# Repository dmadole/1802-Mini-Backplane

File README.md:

# 1802-Mini-Backplane

This is a backplane for the [1802/Mini](https://github.com/dmadole/1802-Mini) system. It supports the following features:

* Seven slots using 1x39 single-row header sockets
* Power, reset, and, and input pushbuttons
* Power input via mini-USB or 2.1mm barrel jack
* USB pass-through header, can also be used for power
* Boards can be coupled end-to-end to make larger backplanes
* PCB can also be assembled as a slot extender card
* Optional pull-up resistors for TPA, TPB, and CLOCK

Gerber files for the PCBs and PDF schematics can be found in [Releases](https://github.com/dmadole/1802-Mini-Backplane/releases).

BOMS and any applicable errata or other notes can be found in [notes](https://github.com/dmadole/1802-Mini-Backplane/tree/main/notes).

For availability of kits and bare PCBs please see http://madole.net/1802/mini/kits

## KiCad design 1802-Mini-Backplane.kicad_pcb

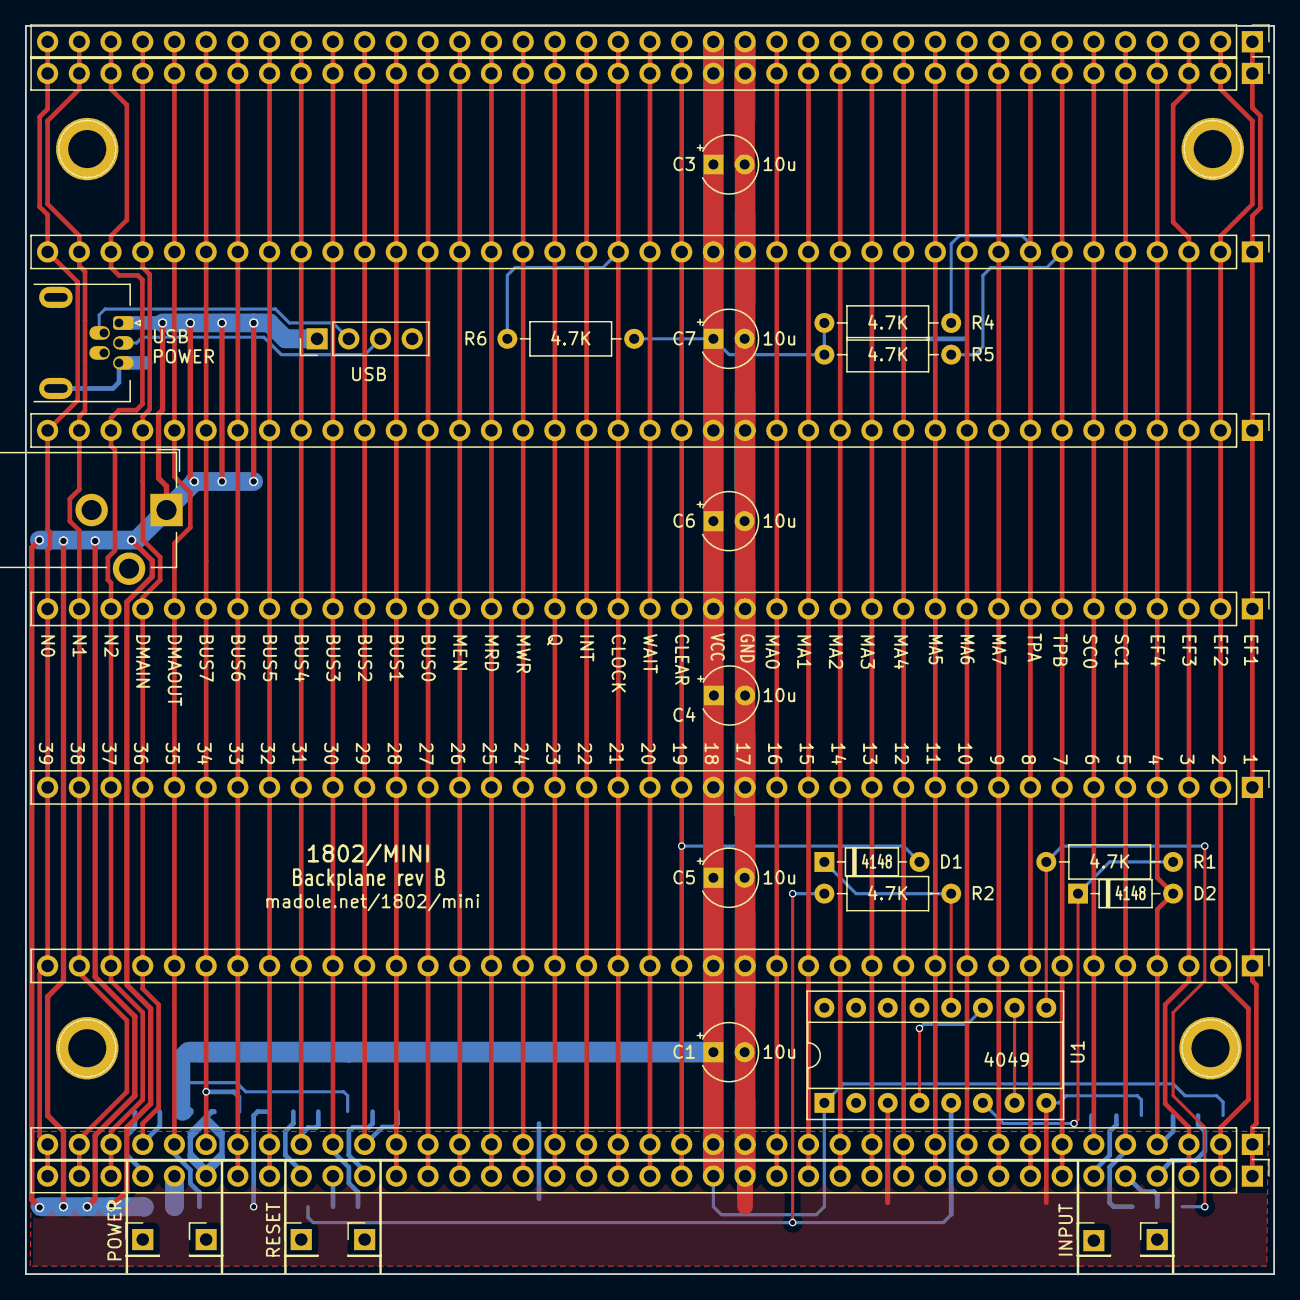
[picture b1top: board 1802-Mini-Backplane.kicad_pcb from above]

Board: 2 copper layers, 100.0 x 100.0 mm, 45 parts (0 on the bottom side), 57 nets.

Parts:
C1, C3, C4, C5, C6, C7: 10uF; CP_Radial_Tantal_D4.5mm_P2.50mm
D1, D2: 1N4148; D_DO-35_SOD27_P7.62mm_Horizontal
J1: Barrel_Jack_Switch; BarrelJack_CUI_PJ-102AH_Horizontal
J2, J3, J4, J5, J6, J7, J8, J14, J15: Expansion; PinHeader_1x39_P2.54mm_Vertical
J9, J10, J11, J12: Mount; 1pin
J13: 56579-0519; USB_Mini-AB_Molex_56579_0519
J16, J17, J18, J19, J20, J21: Mount; PinHeader_1x01_P2.54mm_Vertical
J22: Conn_01x04; PinHeader_1x04_P2.54mm_Vertical
JP1, JP2, JP3, JP4, JP5, JP6, JP7, JP8, JP9: Jumper_3_Open; SolderJumper-3_P2.0mm_Open_TrianglePad1.0x1.5mm_NumberLabels
R1, R2, R4, R5, R6: 4.7K; R_Axial_DIN0207_L6.3mm_D2.5mm_P10.16mm_Horizontal
U1: 4049; DIP-16_W7.62mm_Socket

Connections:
/BUS0: J2.27, J3.27, J4.27, J5.27, J6.27, J7.27, J8.27, J14.27, J15.27
/BUS1: J2.28, J3.28, J4.28, J5.28, J6.28, J7.28, J8.28, J14.28, J15.28
/BUS2: J2.29, J3.29, J4.29, J5.29, J6.29, J7.29, J8.29, J14.29, JP4.3
/BUS3: J2.30, J3.30, J4.30, J5.30, J6.30, J7.30, J8.30, J14.30, JP5.3
/BUS4: J2.31, J3.31, J4.31, J5.31, J6.31, J7.31, J8.31, J14.31, JP6.3
/BUS5: J2.32, J3.32, J4.32, J5.32, J6.32, J7.32, J8.32, J14.32, J15.32
/BUS6: J2.33, J3.33, J4.33, J5.33, J6.33, J7.33, J8.33, J14.33, J15.33
/BUS7: J2.34, J3.34, J4.34, J5.34, J6.34, J7.34, J8.34, J14.34, JP7.3
/MA0: J2.16, J3.16, J4.16, J5.16, J6.16, J7.16, J8.16, J14.16, J15.16
/MA1: J2.15, J3.15, J4.15, J5.15, J6.15, J7.15, J8.15, J14.15, J15.15
/MA2: J2.14, J3.14, J4.14, J5.14, J6.14, J7.14, J8.14, J14.14, J15.14
/MA3: J2.13, J3.13, J4.13, J5.13, J6.13, J7.13, J8.13, J14.13, J15.13
/MA4: J2.12, J3.12, J4.12, J5.12, J6.12, J7.12, J8.12, J14.12, J15.12
/MA5: J2.11, J3.11, J4.11, J5.11, J6.11, J7.11, J8.11, J14.11, J15.11
/MA6: J2.10, J3.10, J4.10, J5.10, J6.10, J7.10, J8.10, J14.10, J15.10
/MA7: J2.9, J3.9, J4.9, J5.9, J6.9, J7.9, J8.9, J14.9, J15.9
CLOCK: J2.21, J3.21, J4.21, J5.21, J6.21, J7.21, J8.21, J14.21, J15.21, R6.2
DMA_IN: J2.36, J3.36, J4.36, J5.36, J6.36, J7.36, J8.36, J14.36, JP9.3
DMA_OUT: J2.35, J3.35, J4.35, J5.35, J6.35, J7.35, J8.35, J14.35, JP8.3
EF1: J2.1, J3.1, J4.1, J5.1, J6.1, J7.1, J8.1, J14.1, J15.1
EF2: J2.2, J3.2, J4.2, J5.2, J6.2, J7.2, J8.2, J14.2, J15.2
EF3: J2.3, J3.3, J4.3, J5.3, J6.3, J7.3, J8.3, J14.3, J15.3
EF4: D2.2, J2.4, J3.4, J4.4, J5.4, J6.4, J7.4, J8.4, J14.4, JP1.3
GND: C1.2, C3.2, C4.2, C5.2, C6.2, C7.2, J1.2, J2.17, J3.17, J4.17, J5.17, J6.17, J7.17, J8.17, J13.5, J13.6, J14.17, J15.17, J22.4, JP3.1, JP6.1, U1.3, U1.8, U1.14
INTERRUPT: J2.22, J3.22, J4.22, J5.22, J6.22, J7.22, J8.22, J14.22, J15.22
MEN: J2.26, J3.26, J4.26, J5.26, J6.26, J7.26, J8.26, J14.26, J15.26
MRD: J2.25, J3.25, J4.25, J5.25, J6.25, J7.25, J8.25, J14.25, J15.25
MWR: J2.24, J3.24, J4.24, J5.24, J6.24, J7.24, J8.24, J14.24, J15.24
N0: J2.39, J3.39, J4.39, J5.39, J6.39, J7.39, J8.39, J14.39, J15.39
N1: J2.38, J3.38, J4.38, J5.38, J6.38, J7.38, J8.38, J14.38, J15.38
N2: J2.37, J3.37, J4.37, J5.37, J6.37, J7.37, J8.37, J14.37, J15.37
unnamed: D1.1, R2.1, U1.12
unnamed: D2.1, R1.1, U1.6
unnamed: J1.1, J13.1, J22.1, JP8.1
unnamed: J13.2, J22.2
unnamed: J13.3, J22.3
unnamed: J15.4, JP1.2
unnamed: J15.5, JP2.2
unnamed: J15.6, JP3.2
unnamed: J15.29, JP4.2
unnamed: J15.30, JP5.2
unnamed: J15.31, JP6.2
unnamed: J15.34, JP7.2
unnamed: J15.35, JP8.2
unnamed: J15.36, JP9.2
unnamed: JP2.1, R1.2, U1.9
unnamed: JP5.1, R2.2, U1.5
unnamed: U1.7, U1.10
unnamed: U1.4, U1.11
Q: J2.23, J3.23, J4.23, J5.23, J6.23, J7.23, J8.23, J14.23, J15.23
SC0: J2.6, J3.6, J4.6, J5.6, J6.6, J7.6, J8.6, J14.6, JP3.3
SC1: J2.5, J3.5, J4.5, J5.5, J6.5, J7.5, J8.5, J14.5, JP2.3
TPA: J2.8, J3.8, J4.8, J5.8, J6.8, J7.8, J8.8, J14.8, J15.8, R4.2
TPB: J2.7, J3.7, J4.7, J5.7, J6.7, J7.7, J8.7, J14.7, J15.7, R5.2
VCC: C1.1, C3.1, C4.1, C5.1, C6.1, C7.1, J2.18, J3.18, J4.18, J5.18, J6.18, J7.18, J8.18, J14.18, J15.18, JP1.1, JP4.1, JP7.1, R4.1, R5.1, R6.1, U1.1
~CLEAR: D1.2, J2.19, J3.19, J4.19, J5.19, J6.19, J7.19, J8.19, J14.19, J15.19
~WAIT: J2.20, J3.20, J4.20, J5.20, J6.20, J7.20, J8.20, J14.20, J15.20
